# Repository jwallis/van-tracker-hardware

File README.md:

# van-tracker-hardware
Van Tracker Hardware

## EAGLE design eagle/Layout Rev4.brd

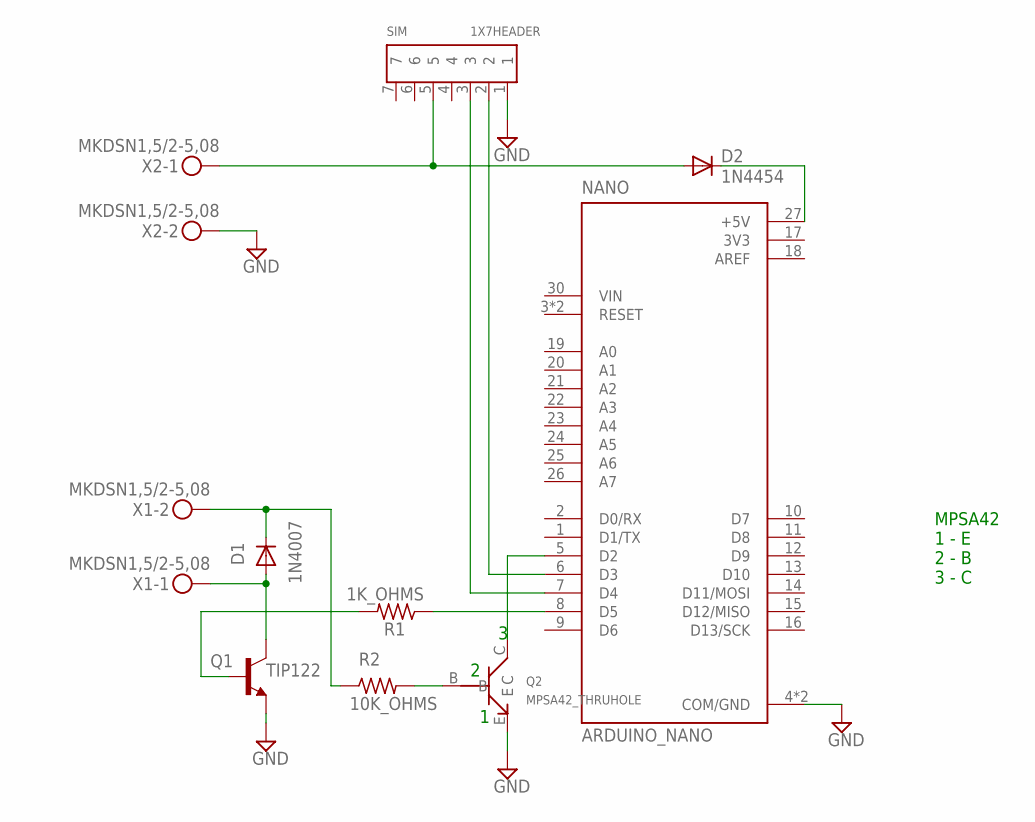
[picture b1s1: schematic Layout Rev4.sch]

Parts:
D1: 1N4007; DO41-10
D2: 1N4454; DO41-10
NANO: ARDUINO_NANO; SHIELD_ARDUINO_NANO
Q1: TIP122; TO220BV
Q2: MPSA42_THRUHOLE; MPSA42
R1: 1K_OHMS; 0207/10
R2: 10K_OHMS; 0207/10
SIM: 1X7HEADER
X1, X2: MKDSN1,5/2-5,08

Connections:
3V3: NANO.17 (3V3)
+5V: D2.A, SIM.5, X2.1
AREF: NANO.18 (AREF)
GND: NANO.4 (COM/GND), NANO.29 (COM/GND), Q1.3 (E), Q2.E, SIM.1, X2.2
unnamed: NANO.7 (D4), SIM.3
unnamed: NANO.6 (D3), SIM.2
unnamed: D1.C, R2.1, X1.2
unnamed: NANO.8 (D5), R1.1
unnamed: D1.A, Q1.2 (C), X1.1
unnamed: Q2.B, R2.2
unnamed: D2.C, NANO.27 (+5V)
unnamed: NANO.5 (D2), Q2.C
unnamed: Q1.1 (B), R1.2

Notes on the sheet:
MPSA42 1 - E 2 - B 3 - C

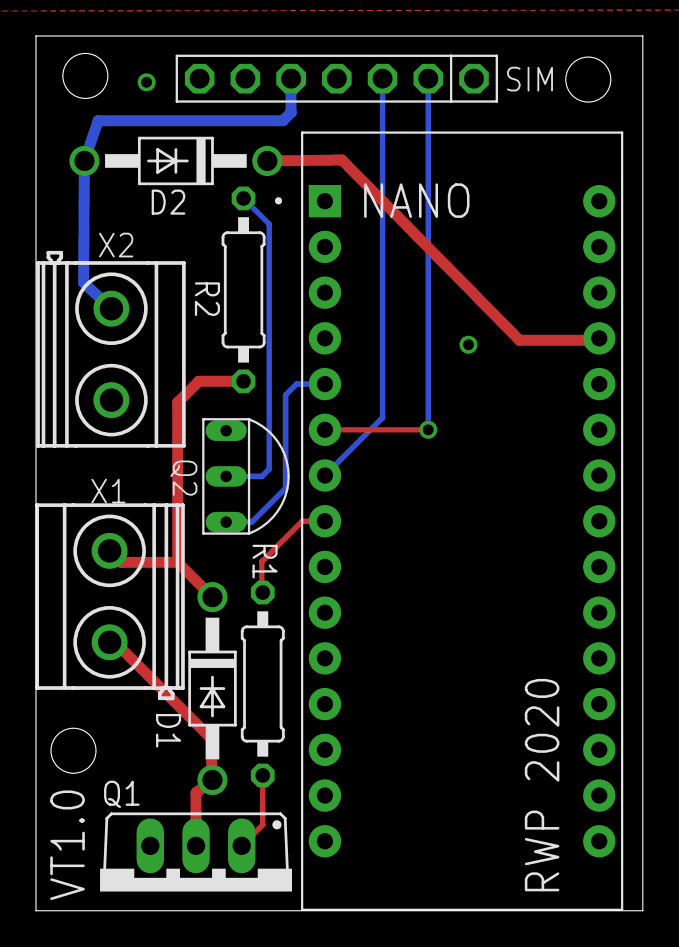
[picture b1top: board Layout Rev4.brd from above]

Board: 2 copper layers, 33.7 x 48.6 mm, 10 parts (0 on the bottom side), 11 nets.

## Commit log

2020-04-21 1.initial revision. Not good because keeping that relay open takes a lot of energy. Need to only open it WHILE the starter is engaged.
2020-04-21 2.failed attempt to use the connection that the kill switch is breaking AS the SIGNAL to break the connection (yeah it didn't work)
2020-04-21 3.to get kill switch signal use interrupt
2020-04-21 1.to get kill switch signal use a second transistor (safer and simpler than interrupt)
2020-04-21 1.add diode going to Arduino +5V pin so we can turn system off and update Arduino via USB. Removed fence and kill switch LEDs
2020-04-21 1.add input signal from starter to D2 using voltage divider in order to send text msg when attempt to start while kill switch is on
2020-04-21 1.Bostig: change voltage divider to transistor. use INPUT_PULLUP in software, so when signal to base of transistor is hot, arduino pin is pulled low. seems like the best way to protect arduino from c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
2020-04-21 1.Use power from starter to power relay coil
2020-05-28 1.kill signal is now also the line that's being interrupted 2.remove starter wire that goes to emergency brake warning light, etc.
2020-08-17 both bostig and stock: 1.change 10K resistor to 4M Ohm 2.make wiring look more like reality so building the hardware is more clear/intuitive including adding jumpers and inputs to PCB
2020-09-26 1.add PCB files, move "Rev" EAGLE files to PCB folder
2020-09-26 1.add all cura files
2020-09-27 1.move models to /models
